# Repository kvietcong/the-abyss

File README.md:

# The Abyss

> I stared into *The Abyss* and it took all my money and time.

A low-profile diode-less 36-key keyboard with nice!view support.
Designed with [Ergogen](https://github.com/ergogen/ergogen) and [Kicad](https://www.kicad.org/).
Meant to be used with [ZMK](https://zmk.dev/).

Named after where too much of my time and money went, *The Abyss*.

A keymap can be found [here](https://github.com/kvietcong/zmk-config/blob/master/config/the_abyss.keymap)
and the shield can be found in [my ZMK config](https://github.com/kvietcong/zmk-config).
Head to the [releases](https://github.com/kvietcong/the-abyss/releases)
to download working ZMK firmware and generated gerbers from the Kicad file.

## Pictures

## Info
> The following is just a long-winded description and commentary of how I
> designed the board, ordered parts, and assembled it.

TODO

## "Review"
> The following is just me rambling about the keyboard and ways I'd might
> change it in another design.

TODO

## Things to do
- Finish up this README.
- Design a carrying case for it.
    - Maybe design a bottom case for it.
- Make a video about it.

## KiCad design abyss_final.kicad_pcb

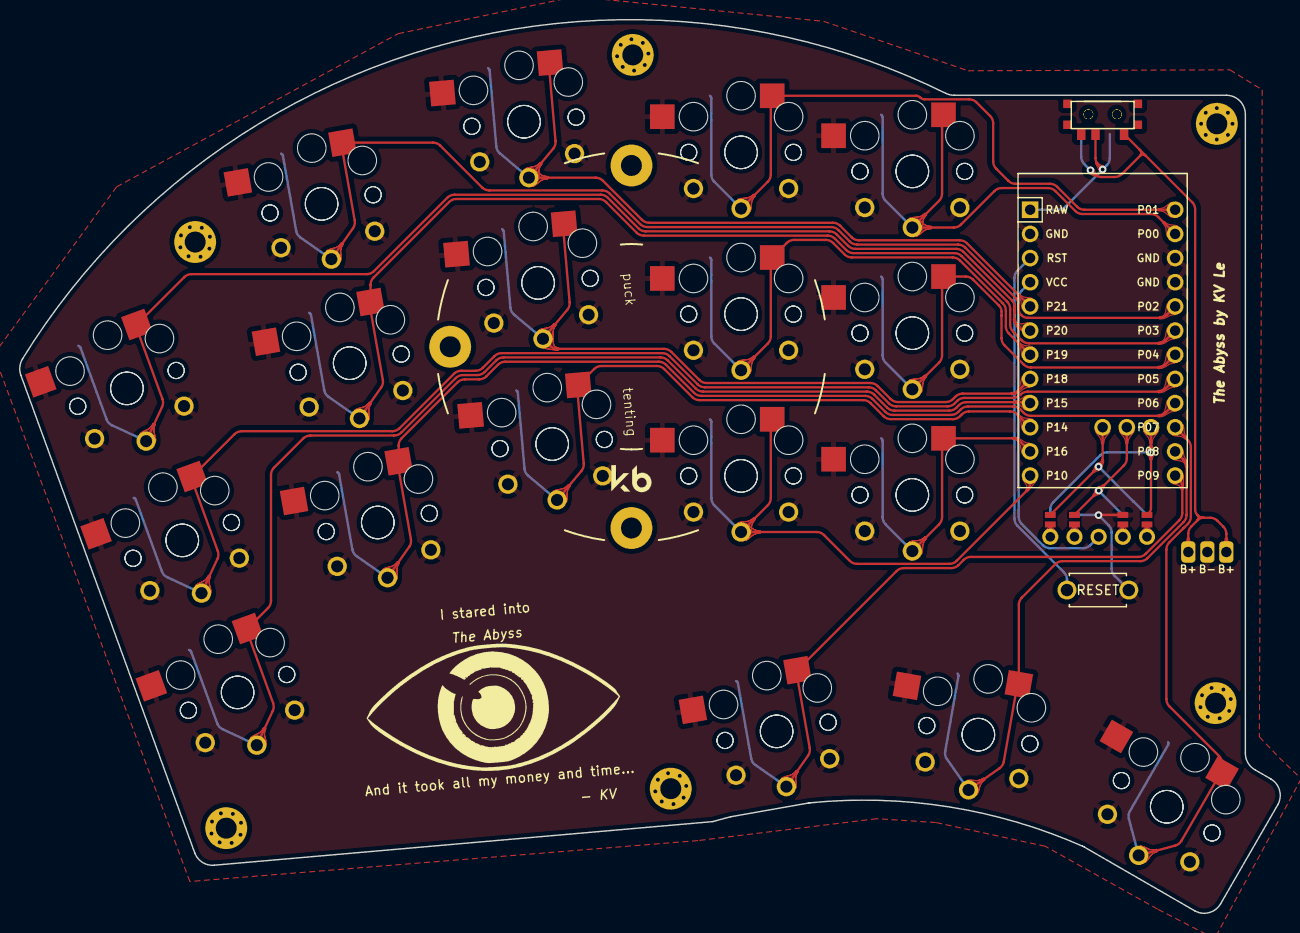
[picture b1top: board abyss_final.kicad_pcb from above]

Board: 2 copper layers, 132.5 x 93.9 mm, 48 parts (0 on the bottom side), 26 nets.

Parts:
B1: ResetSW
HOLE2, HOLE3, HOLE4, HOLE5, HOLE6, HOLE7: MountingHole_2.2mm_M2_Pad_Via
JST1: bat
MCU1: ProMicro
S1, S2, S3, S4, S5, S6, S7, S8, S9, S10, S11, S12, S13, S14, S15, S16, S17, S18, S19, S20, S21, S22, S23, S24, S25, S26, S27, S28, S29, S30, S31, S32, S33, S34, S35, S36: PG1350
T1, T2: SPDT_C128955
nice!view1: nice!view; niceview

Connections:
B+: JST1.1, T1.1, T2.1
CS: MCU1.31, nice!view1.1, nice!view1.5
GND: B1.2, JST1.2, MCU1.2, MCU1.15, MCU1.16, S1.2, S2.2, S3.2, S4.2, S5.2, S6.2, S7.2, S8.2, S9.2, S10.2, S11.2, S12.2, S13.2, S14.2, S15.2, S16.2, S17.2, S18.2, S19.1, S20.1, S21.1, S22.1, S23.1, S24.1, S25.1, S26.1, S27.1, S28.1, S29.1, S30.1, S31.1, S32.1, S33.1, S34.1, S35.1, S36.1, nice!view1.2, nice!view1.4
MOSI: MCU1.33, nice!view1.1, nice!view1.5
RAW: MCU1.1, T1.2, T2.2
RST: B1.1, MCU1.3
SCK: MCU1.32, nice!view1.2, nice!view1.4
VCC: MCU1.4, nice!view1.3
keys_index_bottom: MCU1.12, S10.1, S28.2
keys_index_home: MCU1.7, S11.1, S29.2
keys_index_top: MCU1.13, S12.1, S30.2
keys_inner_bottom: MCU1.11, S13.1, S31.2
keys_inner_home: MCU1.19, S14.1, S32.2
keys_inner_top: MCU1.14, S15.1, S33.2
keys_middle_bottom: MCU1.10, S7.1, S25.2
keys_middle_home: MCU1.8, S8.1, S26.2
keys_middle_top: MCU1.5, S9.1, S27.2
keys_pinky_bottom: MCU1.9, S1.1, S19.2
keys_pinky_home: MCU1.20, S2.1, S20.2
keys_pinky_top: MCU1.6, S3.1, S21.2
keys_ring_bottom: MCU1.21, S4.1, S22.2
keys_ring_home: MCU1.18, S5.1, S23.2
keys_ring_top: MCU1.17, S6.1, S24.2
keys_thumb_home: MCU1.23, S17.1, S35.2
keys_thumb_inner: MCU1.24, S16.1, S34.2
keys_thumb_outer: MCU1.22, S18.1, S36.2

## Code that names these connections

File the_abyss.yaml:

points:
  zones:
    keys:
      key:
        padding: 17
        origin: [0, -17]
        bind: [1, 0]
      columns:
        pinky:
          key:
            splay: 15
            spread: 18
        ring:
          key:
            spread: 17
            stagger: 12
            splay: -10
        middle:
          key:
            spread: 18
            stagger: 5
            splay: -5
        index:
          key:
            spread: 18
            stagger: -5
            splay: -5
        inner:
          key:
            spread: 18
            stagger: -2
      rows:
        bottom: {}
        home: {}
        top: {}
    thumb:
      key:
        padding: 17
        bind: 1
        row_net: R0
      anchor:
        ref: keys_inner_bottom
        shift: [-16, -25]
      columns:
        inner:
          key:
            splay: 10
            origin: [0, 10]
            name: keys_thumb_inner
        home:
          key:
            spread: 18
            splay: -20
            origin: [-10, -10]
            name: keys_thumb_home
        outer:
          key:
            spread: 18
            splay: -20
            origin: [-10, -10]
            name: keys_thumb_outer
            bind: [1, 3, 1, 1]
outlines:
  _raw:
    - what: rectangle
      where: true
      bound: true
      size: [14,14]
  _switch_cutouts:
  - what: rectangle
    where: true
    size: 14
    #size: [18,17]
    bound: false
  _rounded_main:
    - what: circle
      radius: 75
      where:
        ref: keys_middle_top
        shift: [5.5, -65]
    - what: rectangle # left cutoff
      size: 100
      where:
        ref: keys_pinky_home
        shift: [-60, 0]
      operation: subtract
    - what: rectangle # right cutoff
      size: 100
      where:
        ref: keys_index_home
        shift: [80, 2]
      operation: subtract
    - what: rectangle # right cutoff
      size: 50
      where:
        ref: keys_thumb_outer
        shift: [30, 0]
      operation: subtract
    - what: rectangle # right cuttoff for thumb
      size: 50
      where:
        ref: keys_thumb_outer
        shift: [38, 0]
      operation: subtract
    - what: circle # thumb curve cutoff
      radius: 57
      where:
        ref: keys_thumb_home
        shift: [-.75, -65]
      operation: subtract
    - what: rectangle # bottom left cutoff
      size: 100
      where:
        ref: keys_middle_bottom
        shift: [-35, -91]
      operation: subtract
  _rounded_controller_area:
    - what: rectangle
      size: [34, 74]
      where:
        ref: keys_inner_home
        shift: [18, -12]
  _raw_panel:
    - what: outline
      name: _raw
    - what: outline
      name: _rounded_main
    - what: outline
      name: _rounded_controller_area
  panel:
    - what: outline
      name: _raw_panel
      fillet: 2
  switch_plate:
    main:
      what: outline
      name: panel
      fillet: 0.5
    keyholes:
      what: outline
      name: _switch_cutouts
      operation: subtract
cases:
  switchplate:
    - what: outline
      name: switch_plate
      extrude: 1.2
  bottom:
    - what: outline
      name: panel
      extrude: 1.2
pcbs:
  abyss:
    outlines:
      main:
        outline: panel
    footprints:
      choc_hotswap:
        what: choc
        where: true
        params:
          from: "{{name}}"
          to: GND
          keycaps: true
          reverse: true
          hotswap: true
      choc:
        what: choc
        where: true
        adjust:
          rotate: 180
        params:
          to: "{{name}}"
          from: GND
          keycaps: true
          reverse: true
      controller:
        what: nicenano
        where:
          ref: keys_inner_home
          shift: [20, -1]
          rotate: -90
        params:
          orientation: down

          P20: keys_pinky_top
          P5: keys_pinky_home
          P15: keys_pinky_bottom

          P2: keys_ring_top
          P3: keys_ring_home
          P6: keys_ring_bottom

          P21: keys_middle_top
          P18: keys_middle_home
          P14: keys_middle_bottom

          P1: keys_index_top
          P19: keys_index_home
          P10: keys_index_bottom

          P0: keys_inner_top
          P4: keys_inner_home
          P16: keys_inner_bottom

          P9: keys_thumb_inner
          P8: keys_thumb_home
          P7: keys_thumb_outer

          P33: MOSI
          P32: SCK
          P31: CS
      battery_connnector:
        what: reversible_battery
        where:
          ref:
            - keys_inner_bottom
          shift: [31, -6]
        params:
          side: F
          neg: GND
          pos: B+
      power_switch_top:
        what: slider
        where:
          ref: keys_inner_home
          shift: [20, 23]
        params:
          side: F
          from: B+
          to: RAW
      power_switch_bottom:
        what: slider
        where:
          ref: keys_inner_home
          shift: [20, 23]
        params:
          side: B
          from: B+
          to: RAW
      reset:
        what: button2
        where:
          ref:
            - keys_inner_bottom
          shift: [19.5, -10]
          rotate: 180
        params:
          side: F
          from: GND
          to: RST
      niceview:
        what: niceview
        where:
          ref:
            - keys_inner_bottom
          shift: [14.5, -6]
          rotate: 90
        params:
          CS: CS
          SCK: SCK
          MOSI: MOSI
      tenting_puck:
        what: tenting_puck
        adjust:
          shift: [40, 32]
          rotate: -5
      mh1:
        what: mountinghole
        where:
          ref:
            - keys_thumb_outer
          shift: [-1, 12]
      mh2:
        what: mountinghole
        where:
          ref:
            - keys_pinky_bottom
          shift: [-6, -13]
      mh3:
        what: mountinghole
        where:
          ref:
            - keys_pinky_top
          shift: [12, 12]
      mh4:
        what: mountinghole
        where:
          ref:
            - keys_inner_top
          shift: [32, 5]
      mh5:
        what: mountinghole
        where:
          ref:
            - keys_thumb_inner
          shift: [-12, -4]
      mh6:
        what: mountinghole
        where:
          ref:
            - keys_middle_top
          shift: [12, 6]

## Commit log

2023-05-20 👁️ Initial commit for The Abyss
2023-05-20 📖 Update README.md
2023-05-20 📐 Add custom ergogen footprints used
2023-05-20 🖼️ Add pictures
2023-05-20 📖 Add release link to README.md
2023-05-20 🧹 Clean up the README.md
